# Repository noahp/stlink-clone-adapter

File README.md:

[![GitHub Workflow
Status](https://img.shields.io/github/workflow/status/noahp/stlink-clone-adapter/main-ci?style=for-the-badge)](https://github.com/noahp/stlink-clone-adapter/actions)

# stlink-clone-adapter <!-- omit in toc -->

- [Variants](#variants)
  - [Variant 1](#variant-1)
  - [Variant 2](#variant-2)
  - [Variant X](#variant-x)
- [PCB Renders](#pcb-renders)
  - [Variant-1](#variant-1-1)
  - [Variant-2](#variant-2-1)
- [Part list](#part-list)
- [pyocd](#pyocd)

Adapter board for a 2x5 0.1" (2.54mm) header to arm cortex 10-pin connector.

This is useful when connecting ST-Link v2 clones to a standard ARM 2x5 1.27mm
pitch header.

## Variants

I know of 2 variants of the ST-Link v2 clones, with different pinouts on the 2x5 0.1"
(2.54mm) header. Different adapter boards provided for each variant.

One way to distinguish the variants; when unplugged, check for continuity on pins 3+4 or 5+6.

- pins 3+4 shorted, **variant-1**
- pins 5+6 shorted, **variant-2**

### Variant 1

Older model I bought in ~2016.

From the pin 1 marker on the header on the ST-Link, pinout is as follows:

|Funtion|Pin|Pin|Function|
|---|---|---|---|
|RST*|1|2|SWDIO|
|GND*|3|4|GND|
|SWIM|5|6|SWCLK|
|3.3V|7|8|3.3V|
|5.0V|9|10|5.0V|

**Note that the labeling is incorrect for some pins on the etching on the case /
on the silkscreen on the board. My device had the pinout for **Variant-2** on
the etching and just incorrect on the silkscreen markings 🤷.*

### Variant 2

Newer model I bought in 2020.

From the pin 1 marker on the header on the ST-Link, pinout is as follows:

|Funtion|Pin|Pin|Function|
|---|---|---|---|
|RST|1|2|SWCLK|
|SWIW|3|4|SWDIO|
|GND|5|6|GND|
|3.3V|7|8|3.3V|
|5.0V|9|10|5.0V|

Labeling appears to be correct on these devices.

### Variant X

*UNTESTED DESIGN*

Support both pinouts with a 3x4 0.1" header to select between them.

Alternative approaches:

- digital selection (mux the 4 connectors), controlled somehow by the signals.
  this has the defect of additional propogation losses through the mux, and
  complexity in the control circuit
- provide 2 2x5 0.1" headers on the board (would be a funky looking board!). the
  connectors are somewhat expensive at $0.80 @ qty 1 but makes for a simpler
  design
- provide a single 6-pin strip (3.3v, GND, RST, SWDIO, SWCLK, SWO) and use 0.1"
  jumper connectors to wire it to the probe (kinda janky connection vs. single
  connector though).

## PCB Renders

### Variant-1

### Variant-2

## Part list

- [2x5 header](http://www.digikey.com/product-search/en?keywords=SFH11-PBPC-D05-RA-BK)
- [arm 10 pin](http://www.digikey.com/product-detail/en/3220-10-0100-00/1175-1627-ND/3883661)
- [2x4 shunt/jumper](https://www.digikey.com/en/products/detail/amphenol-icc-fci/69145-208LF/1523748) [alternate](https://www.digikey.com/en/products/detail/samtec-inc/MNT-104-BK-G/6613574)

## pyocd

Quick note about using the stlink v2 clones with pyocd; I had the best luck
using the device after updating the firmware using the [official ST
updater](https://www.st.com/en/development-tools/stsw-link007.html):

```bash
❯ java -jar stsw-link007/AllPlatforms/STLinkUpgrade.jar -jtag_swim -force_prog
Firmware version detected: V2J29S7
................Upgrade is successful.
Version read: 2.37.7
```

After upating the version should report `V2J37S7` if you run the updater again.

There's a ton of information out there on the stlink devices themselves (I found
[this](https://hackaday.io/project/162597-st-link-clone-repurposing) helpful).

On ubuntu there's an available package
[stlink-tools](https://packages.ubuntu.com/search?keywords=stlink-tools)
([source](https://github.com/stlink-org/stlink)) which contains some utilities and udev rules for the st-link devices. I didn't end up using the tools themselves
but it could come in handy.

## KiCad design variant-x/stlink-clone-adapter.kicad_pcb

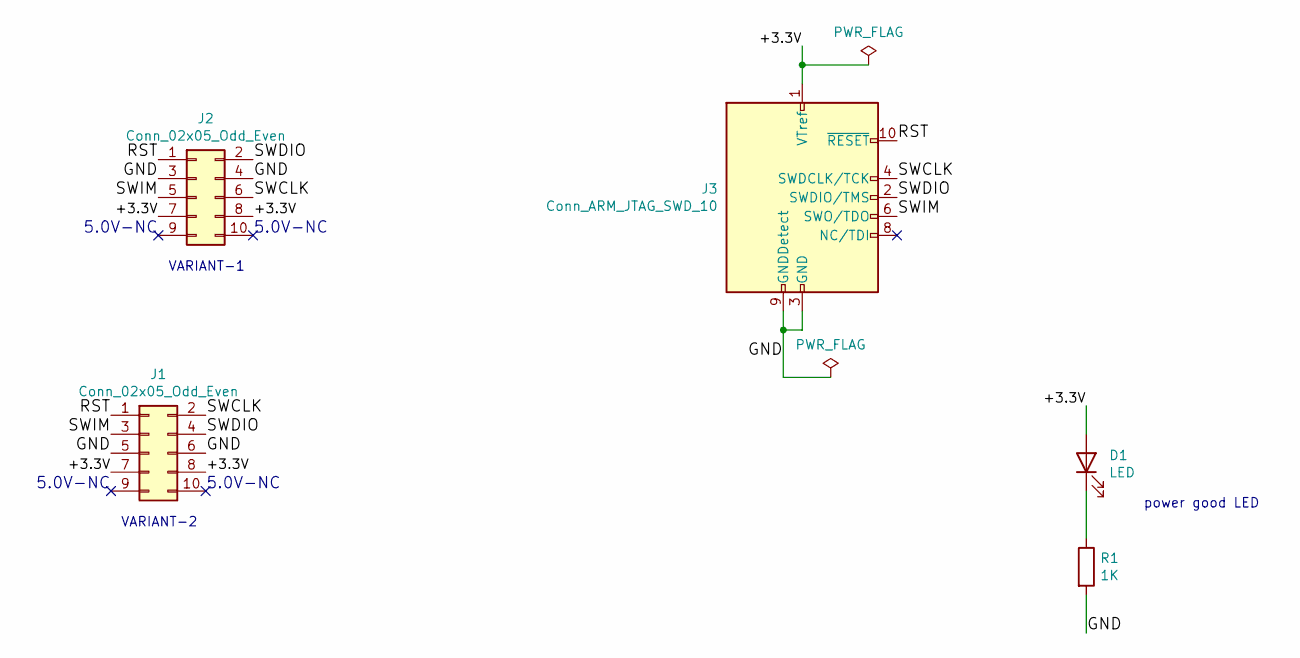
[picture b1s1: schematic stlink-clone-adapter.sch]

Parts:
D1: LED; LED_0603_1608Metric
J1, J2: Conn_02x05_Odd_Even; PinSocket_2x05_P2.54mm_Horizontal
J3: Conn_ARM_JTAG_SWD_10; ARM_10_PIN
R1: 1K; R_0603_1608Metric

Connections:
/+3.3V: D1.2 (A), J1.7, J1.8, J2.7, J2.8, J3.1 (VTref)
/GND: J1.5, J1.6, J2.3, J2.4, J3.3 (GND), J3.5 (GND), J3.9 (GNDDetect), R1.2
/RST: J1.1, J2.1, J3.10 (~RESET~)
/SWCLK: J1.2, J2.6, J3.4 (SWDCLK/TCK)
/SWDIO: J1.4, J2.2, J3.2 (SWDIO/TMS)
/SWIM: J1.3, J2.5, J3.6 (SWO/TDO)
unnamed: D1.1 (K), R1.1

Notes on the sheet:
5.0V-NC
power good LED
VARIANT-2
VARIANT-1

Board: 2 copper layers, 5 parts (0 on the bottom side), 7 nets, no tracks yet.

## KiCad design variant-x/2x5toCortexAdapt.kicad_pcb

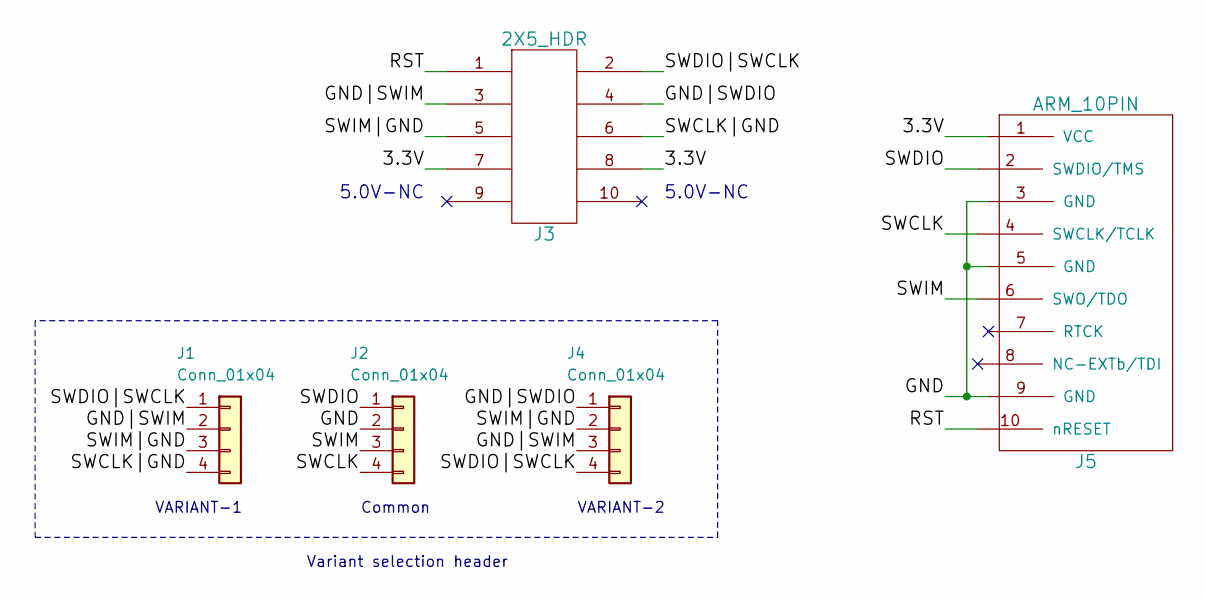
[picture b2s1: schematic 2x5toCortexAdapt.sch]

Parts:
J1, J2, J4: Conn_01x04; PinHeader_1x04_P2.54mm_Vertical
J3: 2X5_HDR; IDC-Header_2x05_P2.54mm_Horizontal
J5: ARM_10PIN; ARM_10_PIN

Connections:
/3.3V: J3.7, J3.8, J5.1 (VCC)
/GND: J2.2, J5.3 (GND), J5.5 (GND), J5.9 (GND)
/GND|SWDIO: J3.4, J4.1
/GND|SWIM: J1.2, J3.3, J4.3
/RST: J3.1, J5.10 (nRESET)
/SWCLK: J2.4, J5.4 (SWCLK/TCLK)
/SWCLK|GND: J1.4, J3.6
/SWDIO: J2.1, J5.2 (SWDIO/TMS)
/SWDIO|SWCLK: J1.1, J3.2, J4.4
/SWIM: J2.3, J5.6 (SWO/TDO)
/SWIM|GND: J1.3, J3.5, J4.2

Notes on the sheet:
5.0V-NC
VARIANT-1
VARIANT-2
Variant selection header
Common

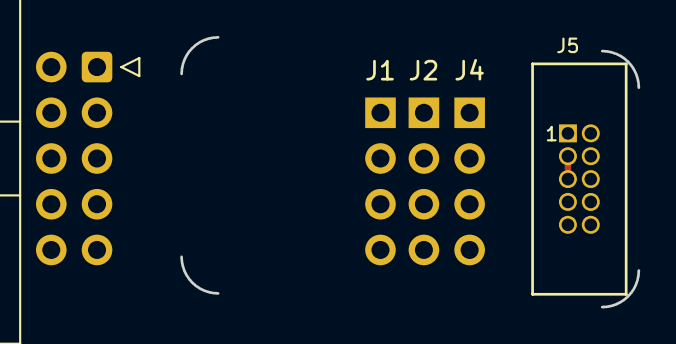
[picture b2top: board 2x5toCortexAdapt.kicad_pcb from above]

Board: 2 copper layers, 25.4 x 15.0 mm, 5 parts (0 on the bottom side), 11 nets.

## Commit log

2015-11-11 layout done.
2015-11-11 add pcb renders
2020-12-14 move to variant-1
2020-12-14 update 3d render for variant-1
2020-12-14 variant-2
2020-12-14 variant-1 v2 update
2020-12-17 update renders
2020-12-17 testing model-viewer
    needs a .glb or .gltf format which I don't know how to convert to >_<
    blender might be able to?
2020-12-17 blender can convert .wrl output woo... no textures tho
2020-12-17 variant-x
2020-12-17 save
2020-12-19 move and rename to stlink-clone-adapter
2020-12-19 variant-x plot done
2020-12-19 remove gerbers. oshpark doesn't need them
2020-12-19 note for jumper
2020-12-19 fix 2x5 header
2020-12-19 1K value for 3.3v status led
2020-12-20 typos
2020-12-23 update gitignore
2020-12-23 kibot
2020-12-23 much smaller base image (700MB vs 7GB)
2020-12-23 remove skip-preflight option
2020-12-24 leftover comment
2020-12-26 try out fillets
2020-12-26 add example 2x4 jumper
2020-12-26 archive kiplot-output
2021-01-02 update with some notes
2021-01-03 pour bottom ground
